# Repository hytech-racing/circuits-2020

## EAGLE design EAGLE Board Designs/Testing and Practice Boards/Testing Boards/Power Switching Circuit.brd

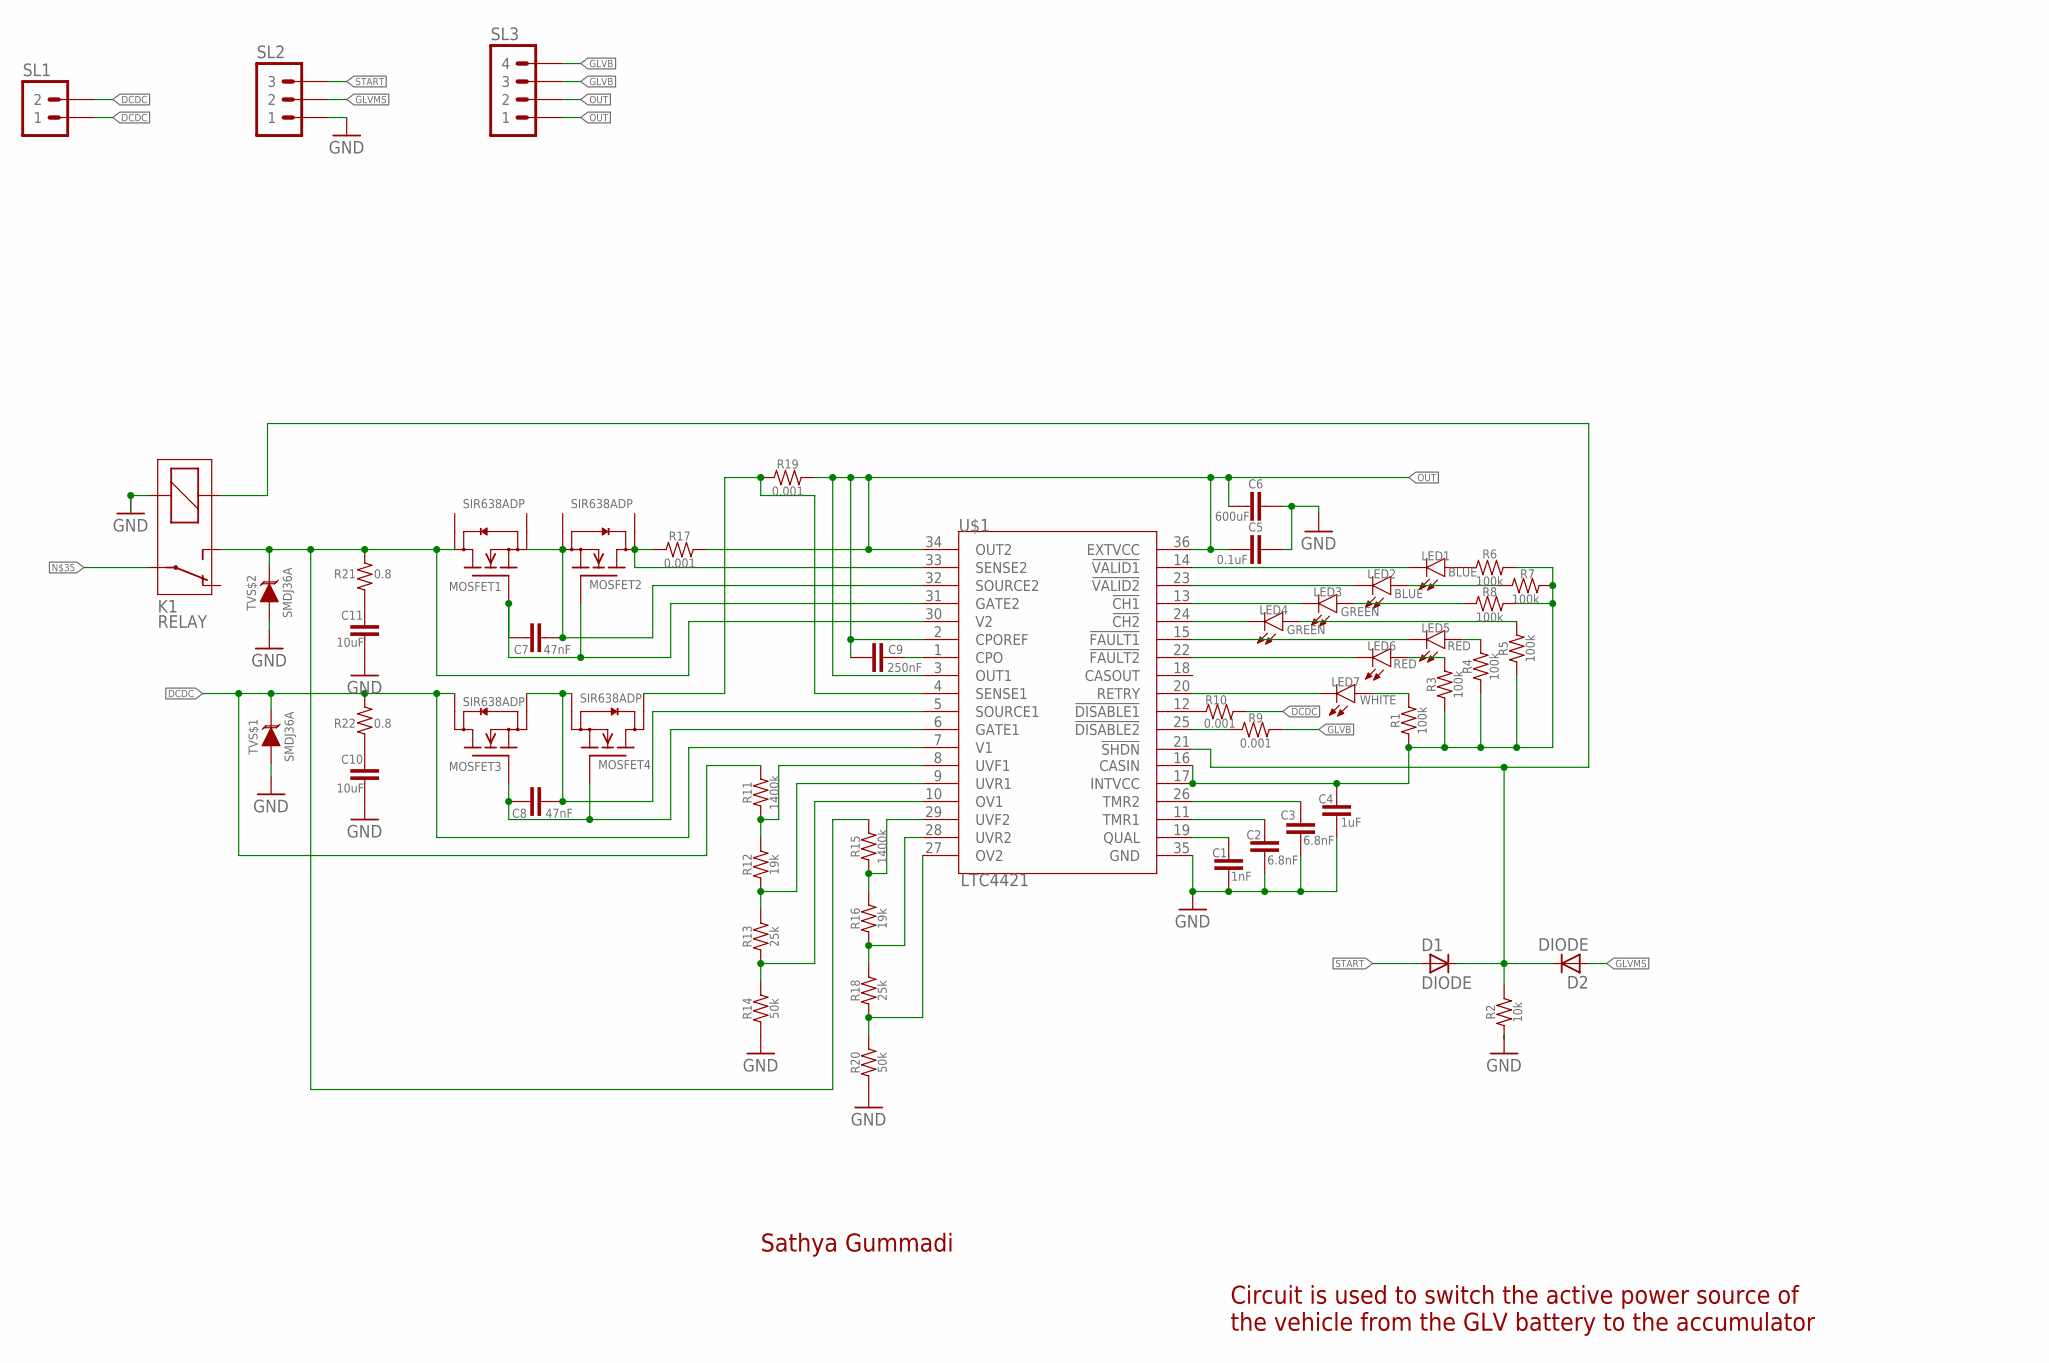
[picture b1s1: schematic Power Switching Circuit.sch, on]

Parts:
C1: 1nF; 0603-CAP
C2, C3: 6.8nF; 0603-CAP
C4: 1uF; 0603-CAP
C5: 0.1uF; 0603-CAP
C6: 600uF; 0603-CAP
C7, C8: 47nF; 0603-CAP
C9: 250nF; 0603-CAP
C10, C11: 10uF; 0603-CAP
LED1, LED2: BLUE; LED-603
LED3, LED4: GREEN; LED-603
LED5, LED6: RED; LED-603
LED7: WHITE; LED-603
MOSFET1, MOSFET2, MOSFET3, MOSFET4: SIR638ADP; SO-8-POWERPAK
R1, R3, R4, R5, R6, R7, R8: 100k; 0603-RES
R2: 10k; 0603-RES
R9, R10, R17, R19: 0.001; 0603-RES
R11, R15: 1400k; 0603-RES
R12, R16: 19k; 0603-RES
R13, R18: 25k; 0603-RES
R14, R20: 50k; 0603-RES
R21, R22: 0.8; 0603-RES
TVS$1, TVS$2: SMDJ36A
U$1: LTC4421; TSSOP-36

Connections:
DCDC: MOSFET3.8 (D), R10.2, R11.2, R22.2, TVS$1.P$2 (C), U$1.7 (V1)
GLVB: MOSFET1.6 (D), R9.2, R15.2, R21.2, TVS$2.P$2 (C), U$1.30 (V2)
GND: C1.2, C2.2, C3.2, C4.2, C5.1, C6.1, C10.2, C11.2, R2.1, R14.1, R20.1, TVS$1.P$1 (A), TVS$2.P$1 (A), U$1.35 (GND)
unnamed: R10.1, U$1.12 (!DISABLE1)
unnamed: C3.1, U$1.26 (TMR2)
unnamed: C2.1, U$1.11 (TMR1)
unnamed: C1.1, U$1.19 (QUAL)
unnamed: LED7.C, U$1.20 (RETRY)
unnamed: LED1.A, R6.1
unnamed: LED4.C, U$1.24 (!CH2)
unnamed: C7.1, MOSFET1.2 (S), MOSFET2.2 (S), U$1.32 (SOURCE2)
unnamed: LED6.C, U$1.22 (!FAULT2)
unnamed: LED5.C, U$1.15 (!FAULT1)
unnamed: LED3.C, U$1.13 (!CH1)
unnamed: LED2.C, U$1.23 (!VALID2)
unnamed: LED1.C, U$1.14 (!VALID1)
unnamed: LED4.A, R5.2
unnamed: LED3.A, R8.1
unnamed: LED2.A, R7.1
unnamed: LED7.A, R1.2
unnamed: R2.2, U$1.21 (!SHDN)
unnamed: LED6.A, R3.2
unnamed: LED5.A, R4.2
unnamed: C4.1, R1.1, R3.1, R4.1, R5.1, R6.2, R7.2, R8.2, U$1.16 (CASIN), U$1.17 (INTVCC)
unnamed: R9.1, U$1.25 (!DISABLE2)
unnamed: R18.1, R20.2, U$1.27 (OV2)
unnamed: R16.1, R18.2, U$1.28 (UVR2)
unnamed: R15.1, R16.2, U$1.29 (UVF2)
unnamed: R11.1, R12.2, U$1.8 (UVF1)
unnamed: C8.1, MOSFET3.4 (S), MOSFET4.4 (S), U$1.5 (SOURCE1)
unnamed: R12.1, R13.2, U$1.9 (UVR1)
unnamed: R13.1, R14.2, U$1.10 (OV1)
unnamed: C11.1, R21.1
unnamed: MOSFET2.6 (D), R17.1, U$1.33 (SENSE2)
unnamed: C7.2, MOSFET1.1 (G), MOSFET2.1 (G), U$1.31 (GATE2)
unnamed: C10.1, R22.1
unnamed: C8.2, MOSFET3.1 (G), MOSFET4.1 (G), U$1.6 (GATE1)
unnamed: C9.1, U$1.1 (CPO)
unnamed: MOSFET4.8 (D), R19.1, U$1.4 (SENSE1)
OUT: C5.2, C6.2, C9.2, R17.2, R19.2, U$1.2 (CPOREF), U$1.3 (OUT1), U$1.34 (OUT2), U$1.36 (EXTVCC)

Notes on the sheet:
Sathya Gummadi
Circuit is used to switch the active power source of the vehicle from the GLV battery to the accumulator

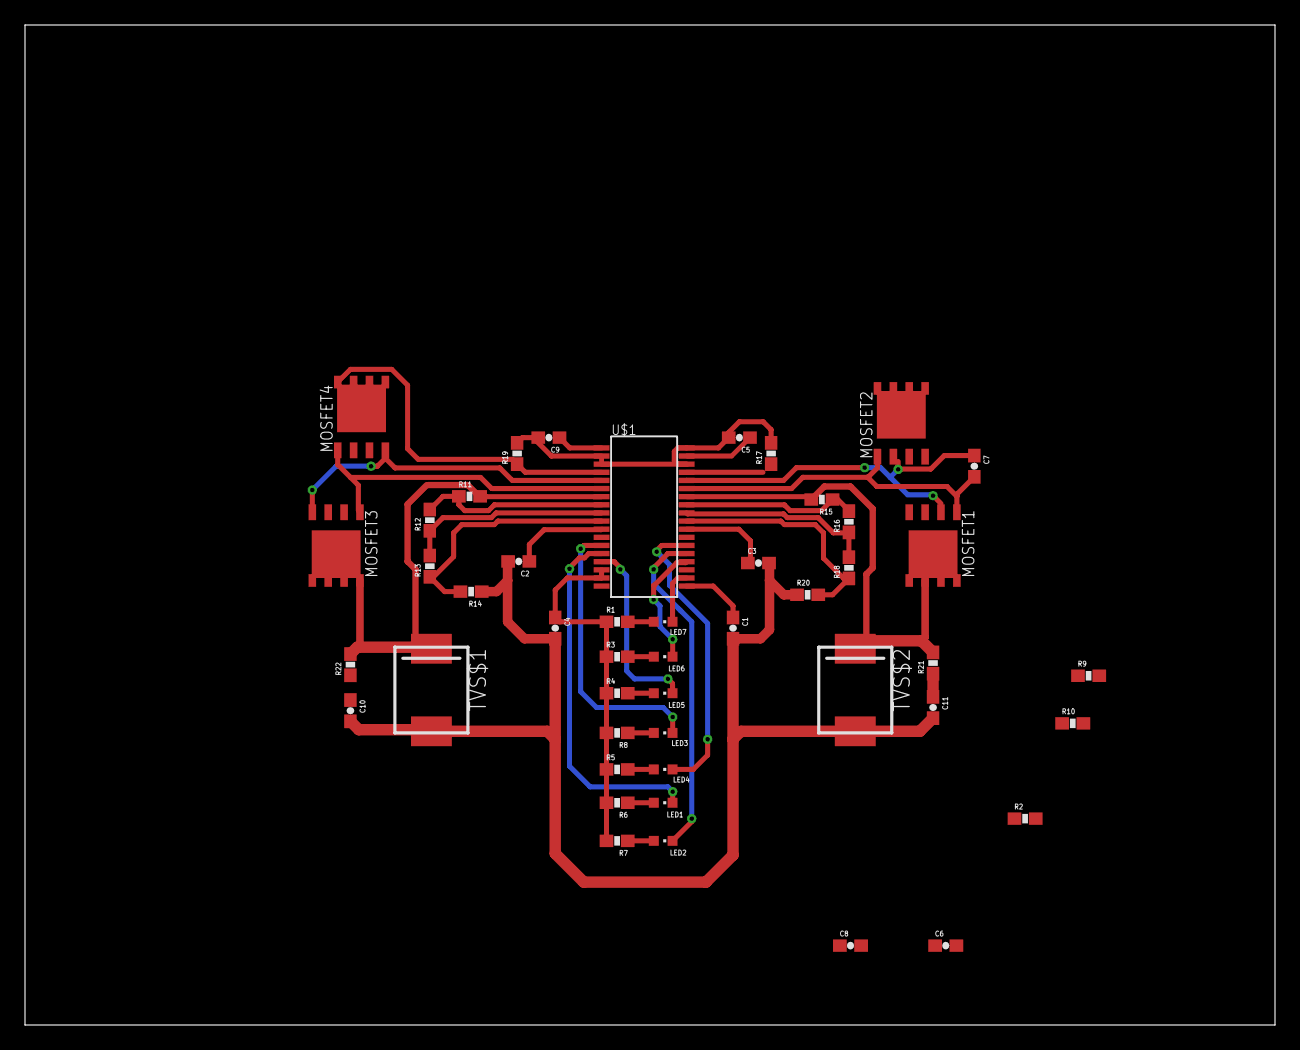
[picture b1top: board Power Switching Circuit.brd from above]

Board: 2 copper layers, 100.0 x 80.0 mm, 47 parts (0 on the bottom side), 40 nets.

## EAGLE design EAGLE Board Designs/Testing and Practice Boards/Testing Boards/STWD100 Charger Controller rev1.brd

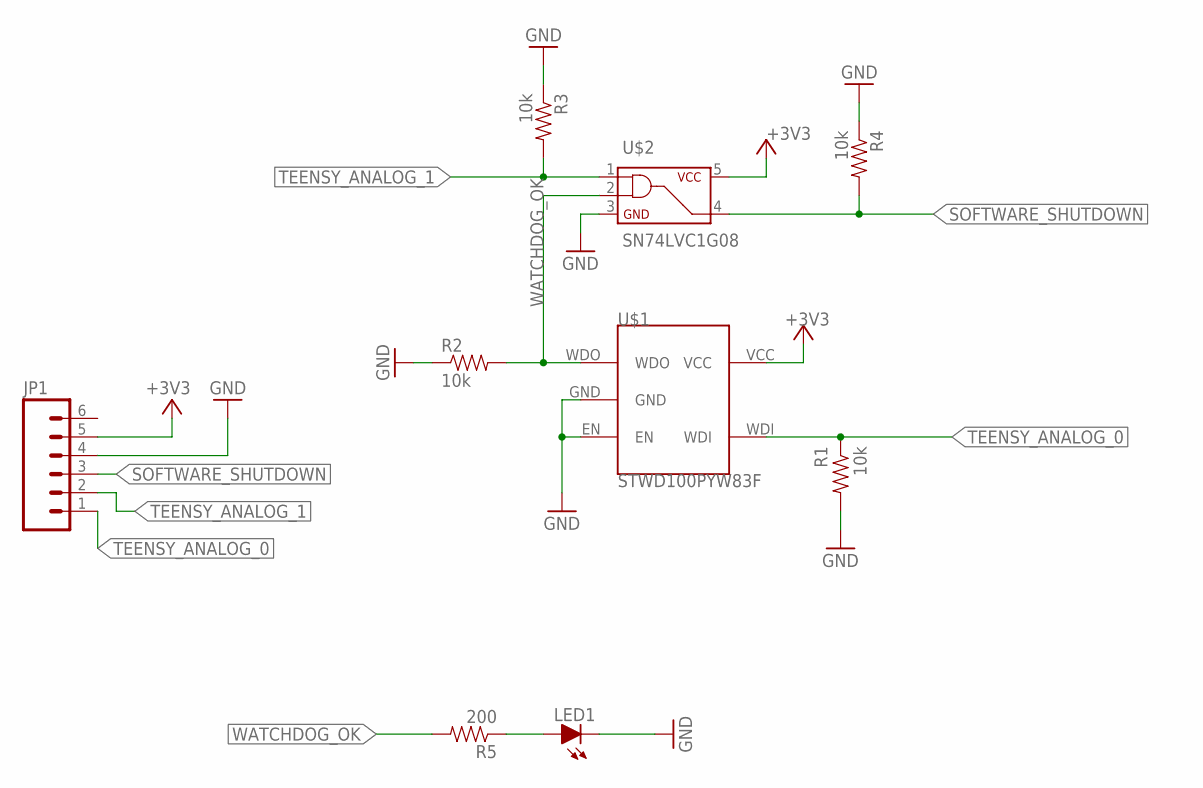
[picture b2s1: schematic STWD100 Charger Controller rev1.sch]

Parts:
JP1: M06; 1X06
LED1: LED-0603; LED-603
R1, R2, R3, R4: 10k; 0603-RES
R5: 200; 0603-RES
U$1: STWD100PYW83F; SOT323-5
U$2: SN74LVC1G08; SOT-23-5

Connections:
+3V3: JP1.5, U$1.VCC, U$2.5
GND: JP1.4, LED1.C, R1.2, R2.1, R3.1, R4.1, U$1.EN, U$1.GND, U$2.3
unnamed: LED1.A, R5.1
SOFTWARE_SHUTDOWN: JP1.3, R4.2, U$2.4
TEENSY_ANALOG_0: JP1.1, R1.1, U$1.WDI
TEENSY_ANALOG_1: JP1.2, R3.2, U$2.1
WATCHDOG_OK: R2.2, R5.2, U$1.WDO, U$2.2

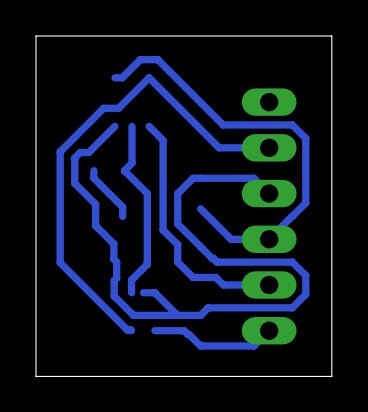
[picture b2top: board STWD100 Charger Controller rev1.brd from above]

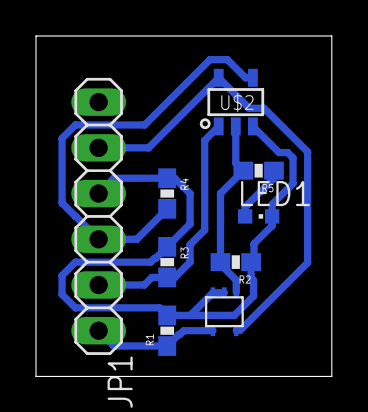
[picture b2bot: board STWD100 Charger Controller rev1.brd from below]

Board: 1 copper layer, 16.4 x 18.9 mm, 9 parts (9 on the bottom side), 7 nets.

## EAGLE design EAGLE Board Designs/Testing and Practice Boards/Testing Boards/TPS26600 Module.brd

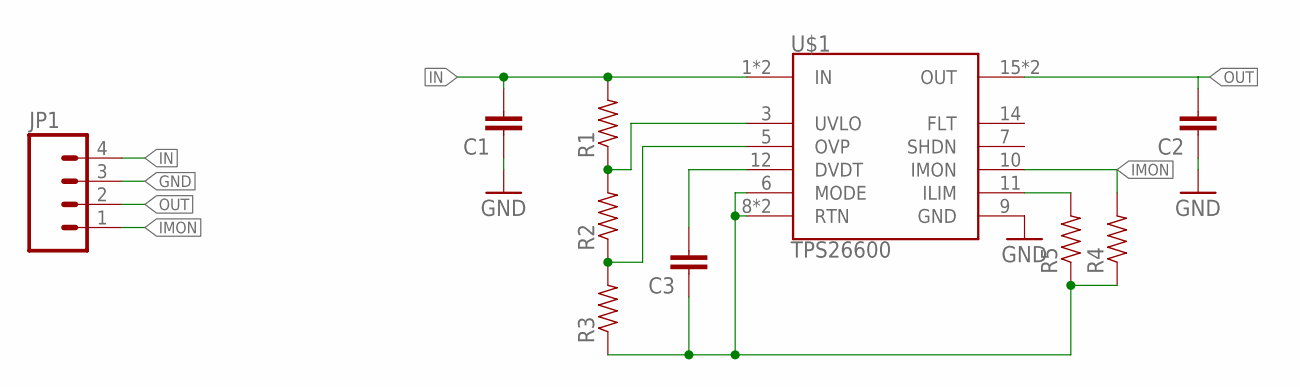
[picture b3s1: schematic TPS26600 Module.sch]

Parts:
C1, C2, C3: CAP0603-CAP; 0603-CAP
JP1: M04_SLIM; 1X04_SLIM
R1, R2, R3, R4, R5: RESISTOR0603; 0603-RES
U$1: TPS26600; HTSSOP-16

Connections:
GND: C1.1, C2.1, JP1.3, U$1.9 (GND)
IMON: JP1.1, R4.2, U$1.10 (IMON)
IN: C1.2, JP1.4, R1.2, U$1.1 (IN), U$1.2 (IN)
unnamed: R1.1, R2.2, U$1.3 (UVLO)
unnamed: R2.1, R3.2, U$1.5 (OVP)
unnamed: C3.2, U$1.12 (DVDT)
unnamed: R5.2, U$1.11 (ILIM)
unnamed: C3.1, R3.1, R4.1, R5.1, U$1.6 (MODE), U$1.8 (RTN), U$1.PAD (RTN)
OUT: C2.2, JP1.2, U$1.15 (OUT), U$1.16 (OUT)

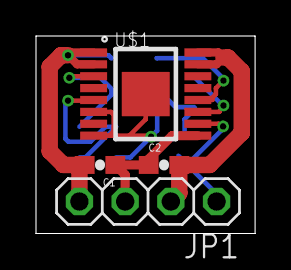
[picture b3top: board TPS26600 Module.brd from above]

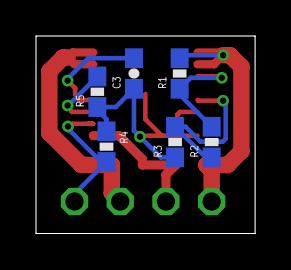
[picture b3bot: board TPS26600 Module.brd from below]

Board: 2 copper layers, 12.2 x 11.0 mm, 10 parts (6 on the bottom side), 9 nets.

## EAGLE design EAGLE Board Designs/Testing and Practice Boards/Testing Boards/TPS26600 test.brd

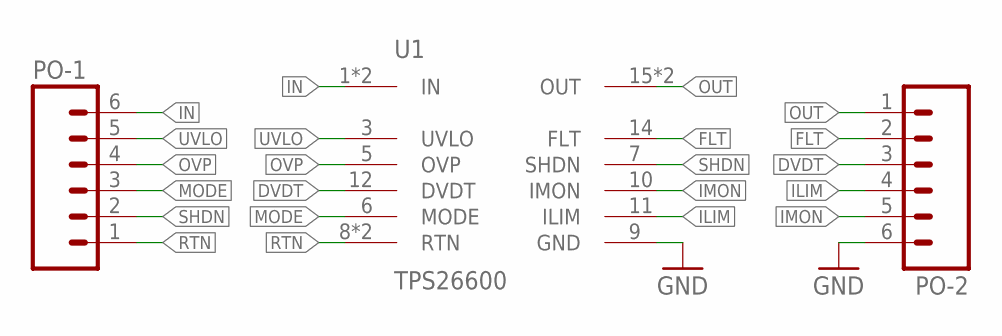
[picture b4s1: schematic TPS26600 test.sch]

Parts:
PO-1, PO-2: M06; 1X06
U1: TPS26600; HTSSOP-16

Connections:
DVDT: PO-2.3, U1.12 (DVDT)
FLT: PO-2.2, U1.14 (FLT)
GND: PO-2.6, U1.9 (GND)
ILIM: PO-2.4, U1.11 (ILIM)
IMON: PO-2.5, U1.10 (IMON)
IN: PO-1.6, U1.1 (IN), U1.2 (IN)
MODE: PO-1.3, U1.6 (MODE)
OUT: PO-2.1, U1.15 (OUT), U1.16 (OUT)
OVP: PO-1.4, U1.5 (OVP)
RTN: PO-1.1, U1.8 (RTN), U1.PAD (RTN)
SHDN: PO-1.2, U1.7 (SHDN)
UVLO: PO-1.5, U1.3 (UVLO)

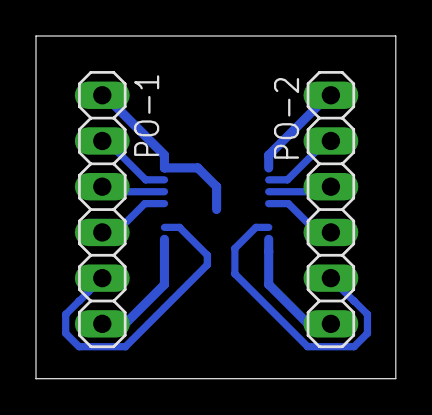
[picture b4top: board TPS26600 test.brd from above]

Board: 1 copper layer, 20.0 x 19.0 mm, 3 parts (1 on the bottom side), 12 nets.

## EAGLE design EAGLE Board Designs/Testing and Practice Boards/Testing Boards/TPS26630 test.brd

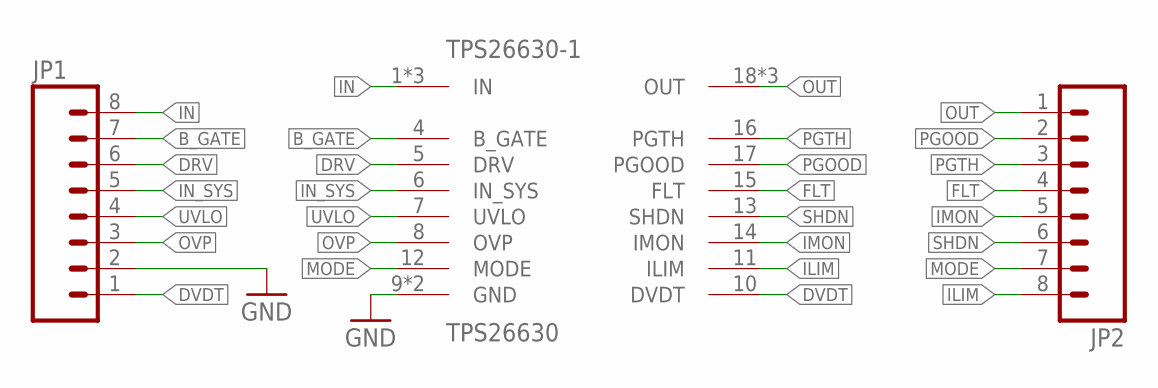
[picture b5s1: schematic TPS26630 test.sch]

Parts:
JP1, JP2: M08; 1X08
TPS26630-1: TPS26630; HTSSOP-20

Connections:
B_GATE: JP1.7, TPS26630-1.4 (B_GATE)
DRV: JP1.6, TPS26630-1.5 (DRV)
DVDT: JP1.1, TPS26630-1.10 (DVDT)
FLT: JP2.4, TPS26630-1.15 (FLT)
GND: JP1.2, TPS26630-1.9 (GND), TPS26630-1.PAD (GND)
ILIM: JP2.8, TPS26630-1.11 (ILIM)
IMON: JP2.5, TPS26630-1.14 (IMON)
IN: JP1.8, TPS26630-1.1 (IN), TPS26630-1.2 (IN), TPS26630-1.3 (IN)
IN_SYS: JP1.5, TPS26630-1.6 (IN_SYS)
MODE: JP2.7, TPS26630-1.12 (MODE)
OUT: JP2.1, TPS26630-1.18 (OUT), TPS26630-1.19 (OUT), TPS26630-1.20 (OUT)
OVP: JP1.3, TPS26630-1.8 (OVP)
PGOOD: JP2.2, TPS26630-1.17 (PGOOD)
PGTH: JP2.3, TPS26630-1.16 (PGTH)
SHDN: JP2.6, TPS26630-1.13 (SHDN)
UVLO: JP1.4, TPS26630-1.7 (UVLO)

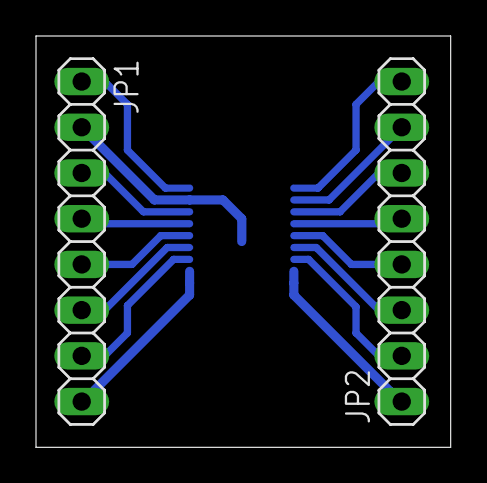
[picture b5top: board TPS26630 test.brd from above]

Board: 1 copper layer, 23.0 x 22.9 mm, 3 parts (1 on the bottom side), 16 nets.

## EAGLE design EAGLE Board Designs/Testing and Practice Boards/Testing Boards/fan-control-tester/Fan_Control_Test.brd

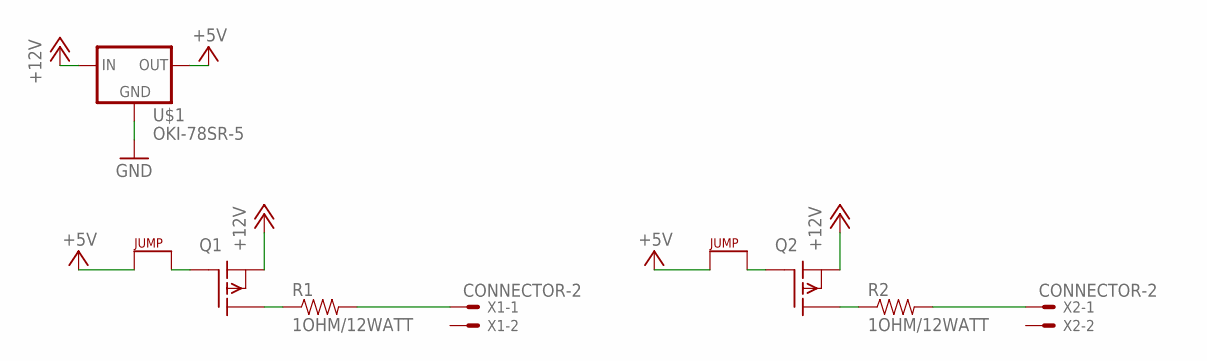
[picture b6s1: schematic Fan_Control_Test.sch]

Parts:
J1, J3: JUMPER.1; 1X02
Q1, Q2: P-CHANNEL_MOSFET_DMP3099L-7; SOT23
R1, R2: 1OHM/12WATT; 10W_RESISTOR_VISHAY
U$1: OKI-78SR-5; OKI-78SR
X1, X2: CONNECTOR-2; MINIFIT_5566-2

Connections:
+5V: J1.1, J3.1, U$1.3 (OUT)
+12V: Q1.2 (S), Q2.2 (S), U$1.1 (IN)
GND: U$1.2 (GND)
unnamed: Q1.3 (D), R1.1
unnamed: J1.2, Q1.1 (G)
unnamed: R1.2, X1.1
unnamed: Q2.3 (D), R2.1
unnamed: J3.2, Q2.1 (G)
unnamed: R2.2, X2.1

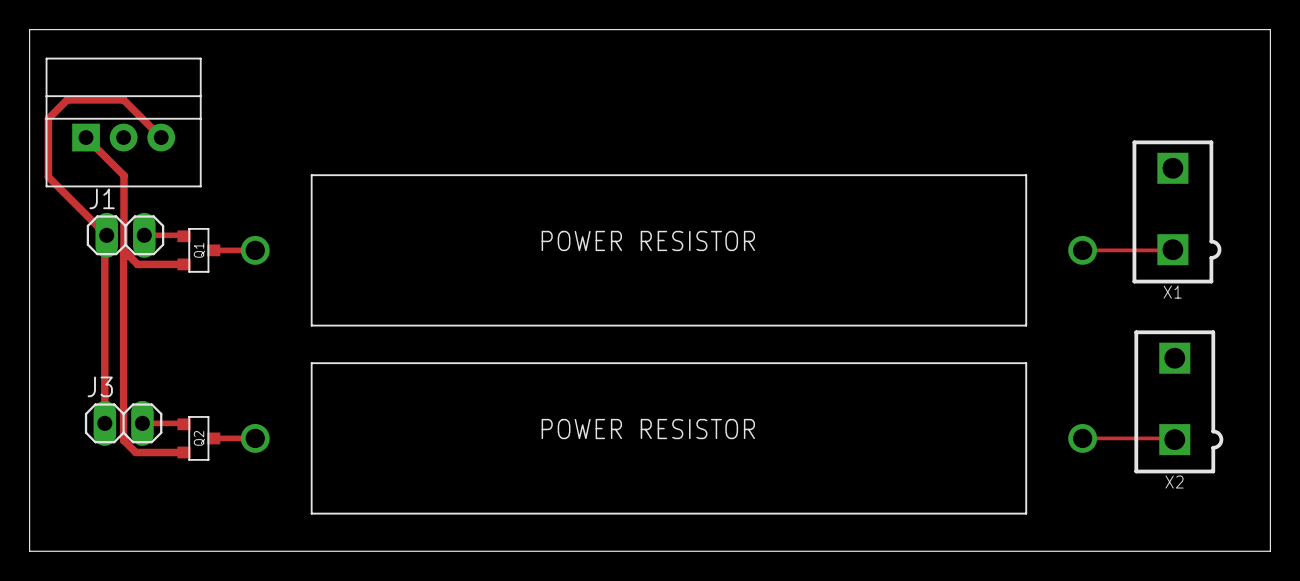
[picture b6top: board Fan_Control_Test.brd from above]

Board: 2 copper layers, 83.8 x 35.2 mm, 9 parts (0 on the bottom side), 8 nets.

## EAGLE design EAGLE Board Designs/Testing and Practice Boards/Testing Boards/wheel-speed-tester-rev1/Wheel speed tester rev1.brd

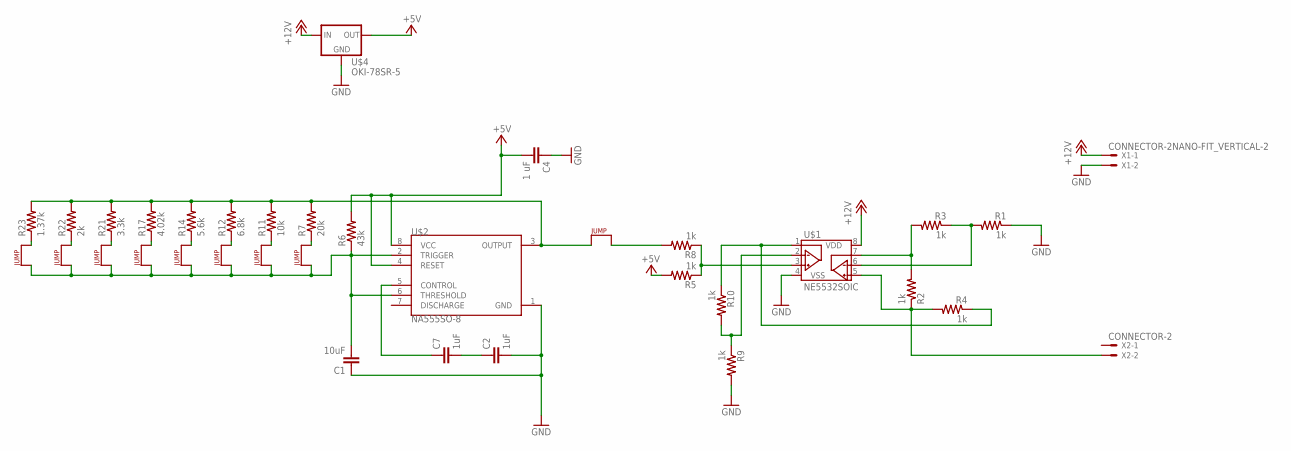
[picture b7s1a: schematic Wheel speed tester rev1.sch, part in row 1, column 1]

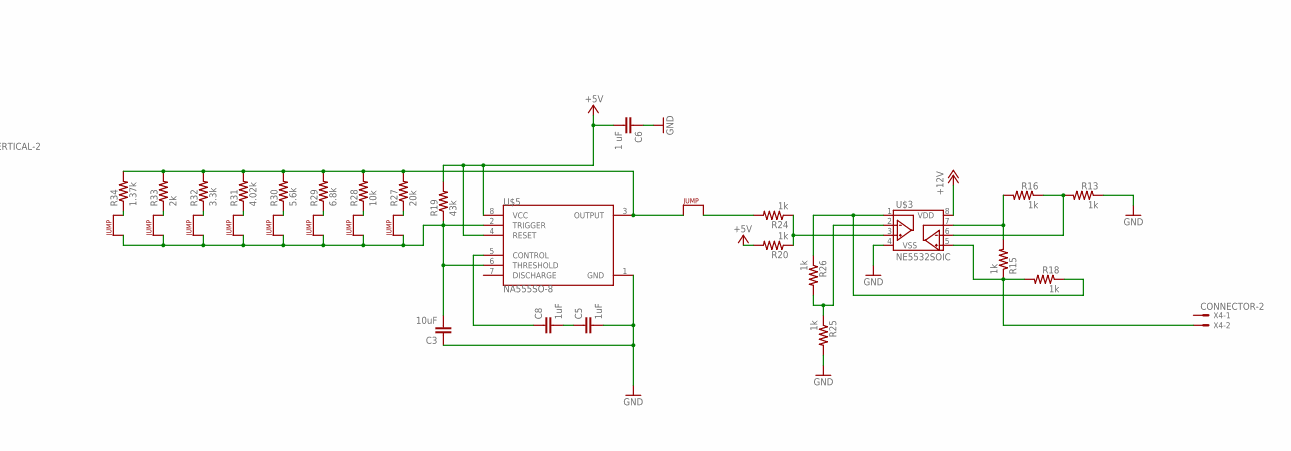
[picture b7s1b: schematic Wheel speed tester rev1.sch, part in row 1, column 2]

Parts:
C1, C3: 10uF; 0603-CAP
C2, C5, C7, C8: 1uF; 0603-CAP
C4, C6: 1 uF; 0603-CAP
J1, J2, J3, J4, J5, J6, J7, J8, J9, J10, J11, J12, J13, J14, J15, J16, J17, J18: JUMPER.1; 1X02
R1, R2, R3, R4, R5, R8, R9, R10, R13, R15, R16, R18, R20, R24, R25, R26: 1k; 0603-RES
R6, R19: 43k; 0603-RES
R7, R27: 20k; 0603-RES
R11, R28: 10k; 0603-RES
R12, R29: 6.8k; 0603-RES
R14, R30: 5.6k; 0603-RES
R17, R31: 4.02k; 0603-RES
R21, R32: 3.3k; 0603-RES
R22, R33: 2k; 0603-RES
R23, R34: 1.37k; 0603-RES
U$1, U$3: NE5532SOIC; SOIC-08
U$2, U$5: NA555SO-8; SOIC-08
U$4: OKI-78SR-5; OKI-78SR
X1: CONNECTOR-2NANO-FIT_VERTICAL-2; NANO-FIT_VERTICAL-2
X2, X4: CONNECTOR-2; MINIFIT_5566-2

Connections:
+5V: C4.2, C6.2, R5.2, R6.2, R19.2, R20.2, U$2.4 (RESET), U$2.8 (VCC), U$4.3 (OUT), U$5.4 (RESET), U$5.8 (VCC)
+12V: U$1.8 (VDD), U$3.8 (VDD), U$4.1 (IN), X1.P$1
ALTERNATINGVOLTAGE: R4.1, R10.1, U$1.1 (VOUTA)
ALTERNATINGVOLTAGE1: R18.1, R26.1, U$3.1 (VOUTA)
GND: C1.1, C2.2, C3.1, C4.1, C5.2, C6.1, R1.1, R9.2, R13.1, R25.2, U$1.4 (VSS), U$2.1 (GND), U$3.4 (VSS), U$4.2 (GND), U$5.1 (GND), X1.P$2
unnamed: R2.2, R3.2, U$1.7 (VOUTB)
unnamed: R1.2, R3.1, U$1.6 (VINB-)
unnamed: C7.1, U$2.5 (CONTROL)
unnamed: J2.2, R8.2
unnamed: C1.2, J1.1, J3.1, J4.1, J5.1, J6.1, J7.1, J8.1, J9.1, R6.1, U$2.2 (TRIGGER), U$2.6 (THRESHOLD)
unnamed: R5.1, R8.1, U$1.3 (VINA+)
unnamed: J9.2, R7.1
unnamed: J2.1, R7.2, R11.2, R12.2, R14.2, R17.2, R21.2, R22.2, R23.2, U$2.3 (OUTPUT)
unnamed: R9.1, R10.2, U$1.2 (VINA-)
unnamed: J8.2, R11.1
unnamed: J7.2, R12.1
unnamed: J6.2, R14.1
unnamed: J5.2, R17.1
unnamed: J4.2, R21.1
unnamed: J3.2, R22.1
unnamed: J1.2, R23.1
unnamed: R13.2, R16.1, U$3.6 (VINB-)
unnamed: J10.1, R27.2, R28.2, R29.2, R30.2, R31.2, R32.2, R33.2, R34.2, U$5.3 (OUTPUT)
unnamed: R20.1, R24.1, U$3.3 (VINA+)
unnamed: R15.2, R16.2, U$3.7 (VOUTB)
unnamed: R25.1, R26.2, U$3.2 (VINA-)
unnamed: C3.2, J11.1, J12.1, J13.1, J14.1, J15.1, J16.1, J17.1, J18.1, R19.1, U$5.2 (TRIGGER), U$5.6 (THRESHOLD)
unnamed: C8.1, U$5.5 (CONTROL)
unnamed: J10.2, R24.2
unnamed: J18.2, R27.1
unnamed: J17.2, R28.1
unnamed: J16.2, R29.1
unnamed: J15.2, R30.1
unnamed: J14.2, R31.1
unnamed: J13.2, R32.1
unnamed: J12.2, R33.1
unnamed: J11.2, R34.1
unnamed: C2.1, C7.2
unnamed: C5.1, C8.2
SENSOROUT: R2.1, R4.2, U$1.5 (VINB+), X2.2
SENSOROUT1: R15.1, R18.2, U$3.5 (VINB+), X4.2

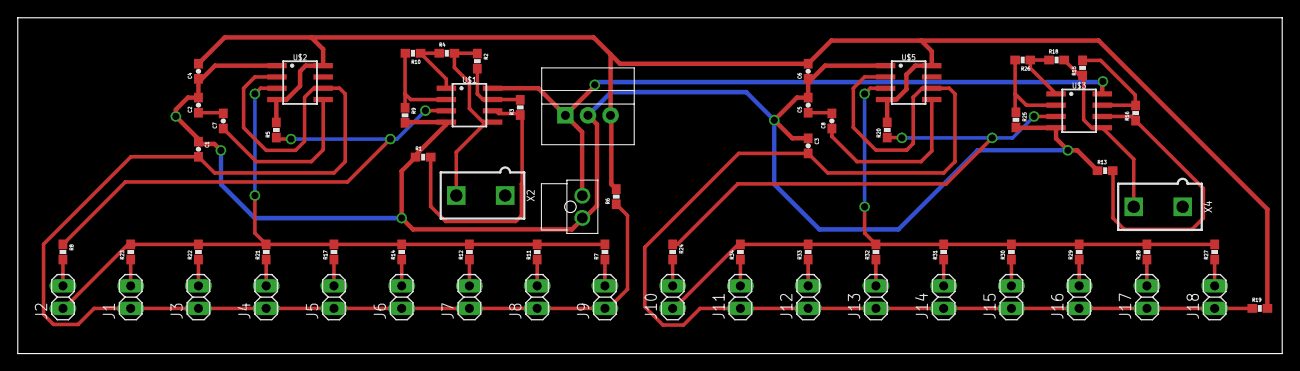
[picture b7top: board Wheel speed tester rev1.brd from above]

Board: 2 copper layers, 142.2 x 37.8 mm, 68 parts (0 on the bottom side), 41 nets.
